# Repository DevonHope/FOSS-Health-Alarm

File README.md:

# NudgeBand

**A small, open-source wristband that wakes you up gently.**

Set a wake-up time, and NudgeBand watches how you move in your sleep. During the 30 minutes before
your alarm, it waits for a moment of light sleep and wakes you with a soft vibration on your wrist,
with no sound and no phone needed. If you never reach light sleep, it still wakes you at your set time.

Everything is open: the circuit boards, the 3D-printed case, the charging dock and the strap pattern.
You can build one yourself.

> **Status:** prototype PCBs ordered (November 2026). Nothing has been built or tested yet.
> See [Current status](#current-status).

---

## How it works

1. **You wear it to bed.** A low-power motion sensor (accelerometer) measures how much you move.
2. **It estimates your sleep stage.** Less movement usually means deeper sleep, and small movements
   usually mean light sleep.
3. **It picks the best moment.** In the 30-minute window before your alarm, it waits for light sleep,
   because waking from light sleep feels easier than waking from deep sleep.
4. **It nudges you awake.** A tiny vibration motor ramps up gently instead of buzzing suddenly.
5. **You put it on the dock.** The dock charges the band and is also used to load new firmware.

The band has no screen and no USB port. It is sealed except for four small gold contacts on the
underside that touch spring pins in the dock.

## What's in it

| Part | What it does |
| --- | --- |
| Nordic nRF54L10 | The main chip, with Bluetooth Low Energy built in |
| Motion sensor (accelerometer) | Tracks movement through the night |
| DRV2605L + 8 mm vibration motor | Gentle, ramped vibration |
| TI BQ25125 | Charges the battery |
| 60 mAh LiPo battery | Expected to last about a month per charge (estimate, not yet measured) |
| RGB LED | Shows status through a thin window in the case, with no hole |

- **Board:** 33 x 15 mm, 4-layer, assembled by JLCPCB
- **Case:** about 45 x 19 x 10 mm, 3D-printed in PETG, held shut by one M2 screw
- **Dock:** USB-C, magnets to hold the band in place, and a built-in programmer (RP2040 running `debugprobe`)
- **Strap:** 16 mm wide, sewn from a free pattern (Velcro or elastic with a buckle)

## Current status

*Last updated: 10 November 2026*

| Area | Status |
| --- | --- |
| Hardware design | ✅ Done. Band and dock **rev C** finished and reviewed (DRC/ERC clean) |
| PCBs | 📦 **Ordered.** Waiting for delivery |
| Case and dock housing | ✅ Designed. Ready to print and test-fit |
| Strap | ✅ Sewing patterns ready |
| Firmware | 🛠️ **Started.** Plan in [`firmware/TODO.md`](firmware/TODO.md); smart-wake logic written and unit-tested, drivers drafted, not yet run on hardware |
| Android app | 🧪 **First version** in [`android/`](android/). Works with a simulated band; Bluetooth spec in [`docs/ble-protocol.md`](docs/ble-protocol.md) |
| Testing | ⏳ Waits for boards. First checks: power-up, charging, radio range, vibration |

**Up next:** assemble the first boards when they arrive, print the case, bring up the firmware
(charger setup, motion sensor, vibration), then test smart-wake on real nights.

**Known limitations:**
- The radio and antenna are not certified (FCC, IC or CE). Treat it as a personal project, not a product.
- The antenna may need tuning on the first boards.
- Battery life is a datasheet estimate until it is measured.

## Repository layout

```
hardware/
├── band/      the wristband: PCB, case and contact carrier for each revision (build rev C)
├── dock/      the charging and programming dock: PCB and housing for each revision (build rev C)
├── strap/     strap sewing patterns (PDF)
├── reviews/   design reviews of the boards
└── tools/     helper scripts (e.g. printability check)
android/       the Android companion app (and a simulated band for testing)
firmware/      band firmware (Zephyr): plan in TODO.md, source, unit tests
docs/          roadmap, parts research, design notes and the Bluetooth protocol
```

Older revisions (A and B) are kept for reference. Each folder has its own README with details.
[`hardware/README.md`](hardware/README.md) lists exactly what to order and what to print.

## Building one

1. **Order the boards.** Use the fab files in `hardware/band/rev-c/pcb/fab/` and `hardware/dock/rev-c/pcb/fab/`
   (JLCPCB with assembly), plus the small contact-carrier board.
2. **Buy the extras.** Spring pins, magnets, battery and motor are listed in
   [`BUY-LIST.md`](hardware/band/rev-a/contact-carrier/BUY-LIST.md).
3. **Print the case and dock** in PETG. Print notes are in each `case/` folder.
4. **Sew the strap** from the pattern in `hardware/strap/`.
5. **Flash the firmware** through the dock (see [`firmware/README.md`](firmware/README.md); not ready yet).

Design tools: KiCad 10 for the PCBs, Python scripts for the case models.

## License

[MIT](LICENSE). Use it, change it and share it.

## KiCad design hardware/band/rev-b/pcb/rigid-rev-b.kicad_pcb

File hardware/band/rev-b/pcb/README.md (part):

> **Superseded by rev C** (2026-11-08 review fixes): [`../../rev-c/pcb`](../../rev-c/pcb)

# WakeBand rigid rev B (KiCad 10 project)

Rev B is rev A rebuilt so that **JLCPCB assembles every part** (no consigned module). It keeps rev
A's 33 x 15 mm outline, 4-layer 0.8 mm stackup (JLC04081H-7628), case, dock, contact carrier and
strap: the four B-side dock landings (J601 1-4 at x 131.5), the LED position (D702) and the cell and
LRA lead pads (TP201/TP202, TP501/TP502, JP201) are where rev A had them.

**Not FCC/IC (or CE) certified.** The radio is a bare nRF54L10 with a chip antenna on our own board,
so the module certification rev A could lean on does not apply. Build it for personal use and
experiments only; don't sell or distribute it as a product.

**Status (2026-11-08):** schematic, placement and routing done. ERC 0; DRC 0 at every severity
(errors and warnings), 0 unconnected, schematic parity 0. Trace audit clean except one forced
0.2 mm jog (see Routing). Not built or tested yet.

## What changed from rev A

| Rev A | Rev B | Why |
| --- | --- | --- |
| ISP2454 module (radio + antenna) | **nRF54L10-QFAA** (C44800139) + Nordic's QFN48 reference circuit + Johanson **2450AT18A0100001E** chip antenna (C17430588) | Module not stocked at JLC. The nRF54L15 (C42458750) is out of stock at JLC and LCSC (0 on 2026-11-07); the L10 has the same package, pins and reference circuit, with 1 MB RRAM / 192 KB RAM. An nRF54L05 or nRF54L15 drops in unchanged. |
| nPM1304 PMIC | **BQ25125** (C2871567) | Same family and pinout as the BQ25120A (C2866577, only 4 at JLC). 4.2 V charge, 30 mA set by R202, 1.8 V buck on at power-up (unused here), LS/LDO switches the LED's supply. **No fuel gauge** (the nPM1304 had one): firmware estimates charge from the BQ's VBMON battery-voltage reading. |
| KTD2026 LED driver | **IS31FL3193** (C2653363) | Stocked; its I2C inputs work on the 2.0 V bus (VIH 1.4 V). |
| 2.0 V rail (nPM1304 buck) | **2.0 V from a TPS7A0220 LDO** (U203, C2860934) on PMID | The BQ25125 buck is 1.8 V +/- 2.5 % (1.755 V worst case), too close to the nRF54L10's 1.75 V power-on-reset minimum, and a board that fails reset can't run firmware to fix it. The LDO is 2.0 V +/- 1.5 % (1.97 V minimum), draws 25 nA, and sits in a 1 x 1 mm X2SON. The buck stays fitted but unloaded (VSYS). A BQ2512x with a higher default (BQ25121A, 2.5 V) has 1 in stock. |
| DRV2605L on VSYS | DRV2605L on **VBAT** | Straight from the cell (2.0-5.2 V). |
| UART pads beside the dock landings, debug LED D701 | **removed** (J601 has the 4 dock landings only) | No routing room at the dock end. Logs go over **SEGGER RTT through the SWD dock pins** (see Firmware setup). |
| I2C/2.0 V test pads TP702-TP704 | removed | Probe R203/R204 and any 2.0 V capacitor instead. |
| R209, R210 (/INT and /PG pull-ups) | removed | No routing room; use the nRF54L10's internal pull-ups on P1.05 and P1.06. |
| KTD2026 on VSYS | IS31FL3193 VCC on **PMID** | Always powered on battery, so its I2C inputs (rated to VCC + 0.3 V) never clamp the shared bus. |

Unchanged: LIS2DW12, DRV2605L, ESD (TPD1E10B06 x4, SMF12A), the dock series resistors.

## nRF54L10 pin map

| Pin | Port | Net | Notes |
| --- | --- | --- | --- |
| 5 | P1.04 | I2C_SCL | clock-capable pin (TWIM needs both lines on clock pins) |
| 9 | P1.08 | I2C_SDA | clock-capable |
| 6 | P1.05 | PMIC_INT | BQ25125 /INT, wake from System OFF (P1) |
| 7 | P1.06 | DOCK_PG | BQ25125 /PG: low while the dock supplies VIN |
| 8 | P1.07 | HAPT_EN | DRV2605L EN |
| 27 | P0.02 | ACC_INT1 | LIS2DW12 INT1, wake (P0) |
| 24 | P0.01 | ACC_INT2 | LIS2DW12 INT2, wake; also TP401 |
| 38 | P1.10 | LED_EN | IS31FL3193 SDB (R211 pulls it low) |
| 39 | P1.11 | CHG_CD | BQ25125 /CD |
| 13 | P2.02 | LS_CTRL | BQ25125 LSCTRL (LED driver supply) |
| 25 / 26 / 30 | SWDIO / SWDCLK / nRESET | dock pins 3/4; TP701 |
| 1 / 2 | XL1 / XL2 | 32.768 kHz crystal X1 |
| 34 / 35 | XC1 / XC2 | 32 MHz crystal X2 |

The pins were chosen for the layout: each signal leaves the QFN on the side facing where it goes.
P1.02/P1.03 (NFC), P2.07/P2.08 and P1.09 (rev A's UART and debug LED) and the other GPIOs are unconnected.

I2C addresses: LIS2DW12 0x19, DRV2605L 0x5A, IS31FL3193 0x68, BQ25125 0x6A.

## Firmware setup

### Logs: SEGGER RTT, no UART

Rev B has no UART pads. Log over **RTT** through the SWD dock pins (J601 3/4) with any J-Link or
the nRF54L DK's on-board debugger: in Zephyr set `CONFIG_USE_SEGGER_RTT=y`, `CONFIG_LOG_BACKEND_RTT=y`
and `CONFIG_UART_CONSOLE=n` (or `CONFIG_RTT_CONSOLE=y`), then read with `JLinkRTTViewer` or
`west rtt`. RTT works on the dock while the band charges. Disable it in release builds so the
debug domain powers down.

### nRF54L10

- **DC/DC:** the board has Nordic's DC/DC inductor (L1 4.7 uH), and all of Nordic's current figures
  assume DC/DC. Turn it on early (`REGULATORS.VREGMAIN.DCDCEN = 1`; in Zephyr set
  `regulator-initial-mode = <NRF5X_REG_MODE_DCDC>` on `&vregmain`).
- **Clocks:** both crystals use the chip's internal load capacitors (no external caps).
  - X1, 32.768 kHz: CL 9 pF.
  - X2, 32 MHz: CL 8 pF.
  - Set `&lfxo` / `&hfxo` to `load-capacitance = "internal"` with the value for each crystal's CL (datasheet INTCAP formula).
  - Use the LFXO as the LF clock source: only the LFXO keeps the GRTC running in System OFF.
- **RF:** the matching network is the board's own (see "Antenna tuning"); leave TX power at 0 dBm
  until it is tuned.
- **NFC pins:** unused; leave NFC disabled.
- **PMIC_INT (P1.05):** enable the internal pull-up (no external resistor). /INT is open drain; with
  EN_INT cleared it only pulses low for 128 us on events.
- **DOCK_PG (P1.06):** enable the internal pull-up (about 13 kOhm; there's no external
  resistor). /PG is open drain and low only while docked, so the pull-up draws about 140 uA
  from the dock and nothing on battery.

### BQ25125

- **/CD:** the BQ25125 talks I2C on battery only while /CD is high.
  - Drive CHG_CD high to configure it. Drive it low to idle: that is Hi-Z mode, where the BQ draws 0.7-0.75 uA. The 2.0 V rail comes from U203 on PMID, so it is unaffected.
  - The buck's 1.8 V output (VSYS) powers nothing, but **leave it on**: the BQ's /CD and LSCTRL input
    thresholds are 0.25 / 0.75 x VSYS, so with SYS off the nRF couldn't reliably drive them. (The I2C
    threshold is 0.75 x the pull-up voltage, 1.5 V on the 2.0 V bus; /CD at 2.0 V is above 0.75 x 1.8 V.)
  - Also drive it low while docked (DOCK_PG low), because /CD high stops charging.
- **Defaults:** without I2C the charger already does the right thing.
  - 1.8 V buck on (unused).
  - 4.2 V charge.
  - 30 mA from R202 (6.65 k) in default mode.
  - 2 mA termination (IPRETERM to GND).
  - 100 mA input limit (ILIM to GND).
  - NTC (TS) enabled.
- **After the first I2C write it is in host mode**, and its 50 s watchdog applies. Write, then re-write at least every 50 s while /CD is high:
  - Charge current 30 mA (reg 0x03, as for the BQ25120A).
  - Termination.
  - EN_INT = 0 in reg 0x02, so /INT pulses instead of staying low through the whole charge.
- **LED supply:** the LED anode (VLED) is on the BQ25125's LS/LDO output, which powers up as a
  1.8 V LDO, too low to light the LED. Write reg 0x07 for load-switch mode (VLED then follows PMID),
  then raise LS_CTRL. The watchdog undoes this after 50 s without I2C in host mode: the LED just
  goes dark, nothing is damaged.
- **Battery level:** read VBMON (reg 0x0A): the battery voltage as a percentage of VBATREG, in 2 % steps.
- **Ship mode:** with VIN absent, /CD high and /MR high, write EN_SHIPMODE. The cell then sees about 2 nA (the DRV2605L on VBAT adds its shutdown current). The dock (VIN) or shorting TP203 (/MR) to GND wakes it; the nRF54L10 then starts from reset.

### IS31FL3193

- **Shutdown by default:** it starts in software shutdown (reg 0x00). Write EN = 1, SSD = 0, set the current with reg 0x03 (e.g. 5 mA), then write PWM and the update register 0x07.
- **Channels:** OUT1 is green, OUT2 blue, OUT3 red (assigned for routing).
- **Supply:** VCC is on PMID (always up on battery), so the I2C bus is never clamped by an
  unpowered driver. Drive LED_EN (SDB) high to wake it. The LED anode is on VLED, which needs
  LS_CTRL on in load-switch mode (see above).

## Antenna tuning

The radio output runs: ANT pin -> Nordic's low-pass ladder (L2 2.7 nH, C6 1.5 pF, L3 3.5 nH, C9 2.0 pF,
L4 3.5 nH, C11 0.3 pF; their exact 0201 parts and placement) -> RF_50 -> **tuning network** -> antenna:

| Part | Position | Fitted | Role |
| --- | --- | --- | --- |
| C14 (0402) | RF_50 to GND, at the ladder end | not fitted | pi shunt 1 |
| R2 (0402) | series, RF_50 to ANT_FEED | 0 ohm | pi series (a 0402 inductor or capacitor) |
| C15 (0402) | ANT_FEED to GND, at the antenna side | not fitted | pi shunt 2 |

The antenna (AE1) sits in a 4.2 x 5.9 mm corner (x 100-104.2, y 109.1-115) with no copper on any
layer (rule area "Antenna keep-out"); the 50-ohm feed (0.36 mm on F.Cu over the In1 ground, 0.16 mm
gap) enters it from the ground edge. Johanson's evaluation board uses 6.5 x 6.5 mm and its own
match, so this board needs its own values. Expect less range than the datasheet until it is tuned.

**Tune with the cell, case, strap and wrist (or a hand) in place:** the plastic, the cell and the
body all pull the antenna down in frequency.

With a VNA (best):
1. Cut the feed at R2: lift R2 and solder a 0402-pad pigtail (a short 1.13 mm coax, shield to the
   C15/C14 ground pads, centre to the AE1 side of R2). Calibrate at the coax end (port extension).
2. Measure S11 of the antenna from 2.3 to 2.6 GHz with the band assembled and on the wrist.
3. Use a Smith-chart tool (e.g. SimSmith or Johanson's own) to pick an L-match with C15 and R2 (or
   a pi with C14) that moves 2.44 GHz to 50 ohm; Murata LQP03/LQG15 inductors and GJM capacitors
   come in 0.1 nH / 0.1 pF steps. Typical starting points for this antenna: series 2-4 nH, shunt
   0.5-1.5 pF.
4. Fit the parts, put R2 back as the series part and re-measure. Aim for S11 below -10 dB across
   2.402-2.480 GHz.

Without a VNA (RSSI method):
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
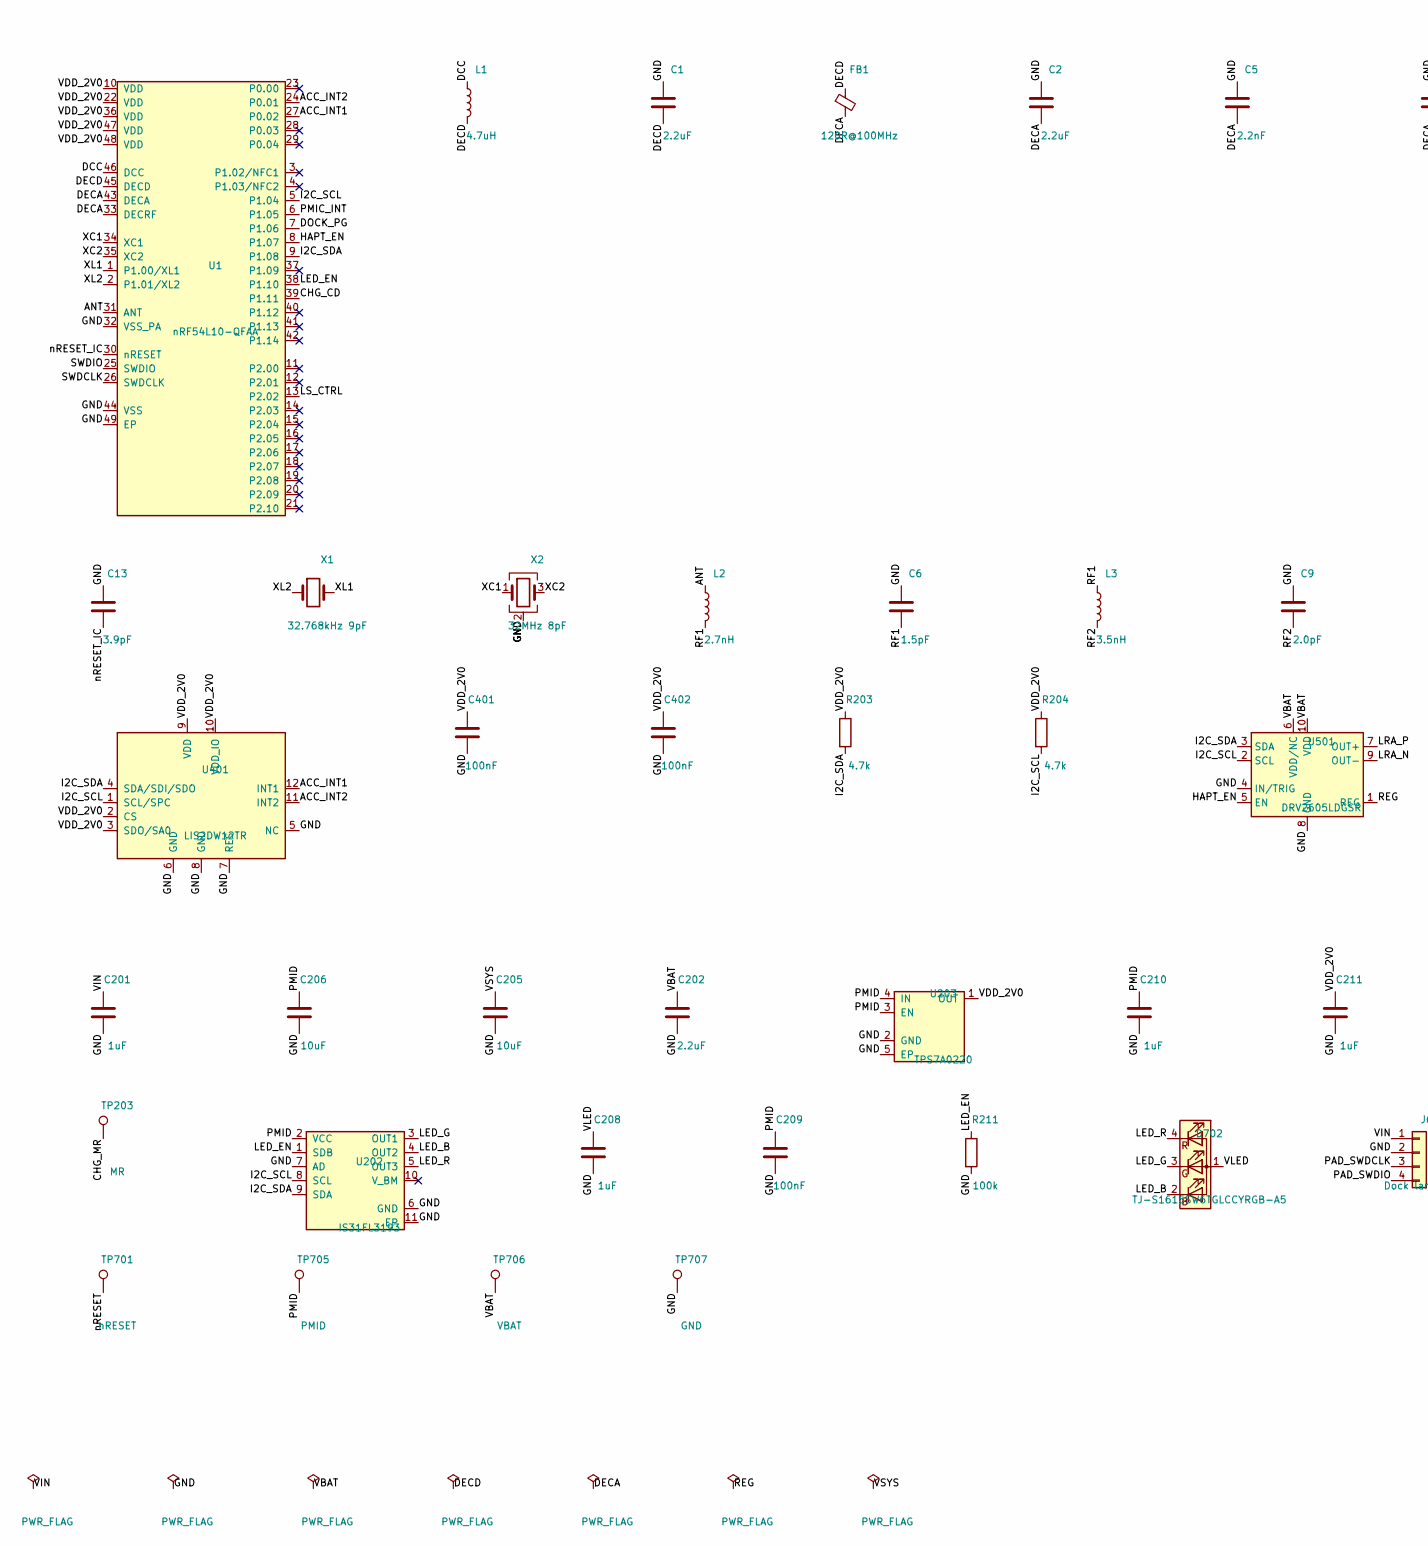
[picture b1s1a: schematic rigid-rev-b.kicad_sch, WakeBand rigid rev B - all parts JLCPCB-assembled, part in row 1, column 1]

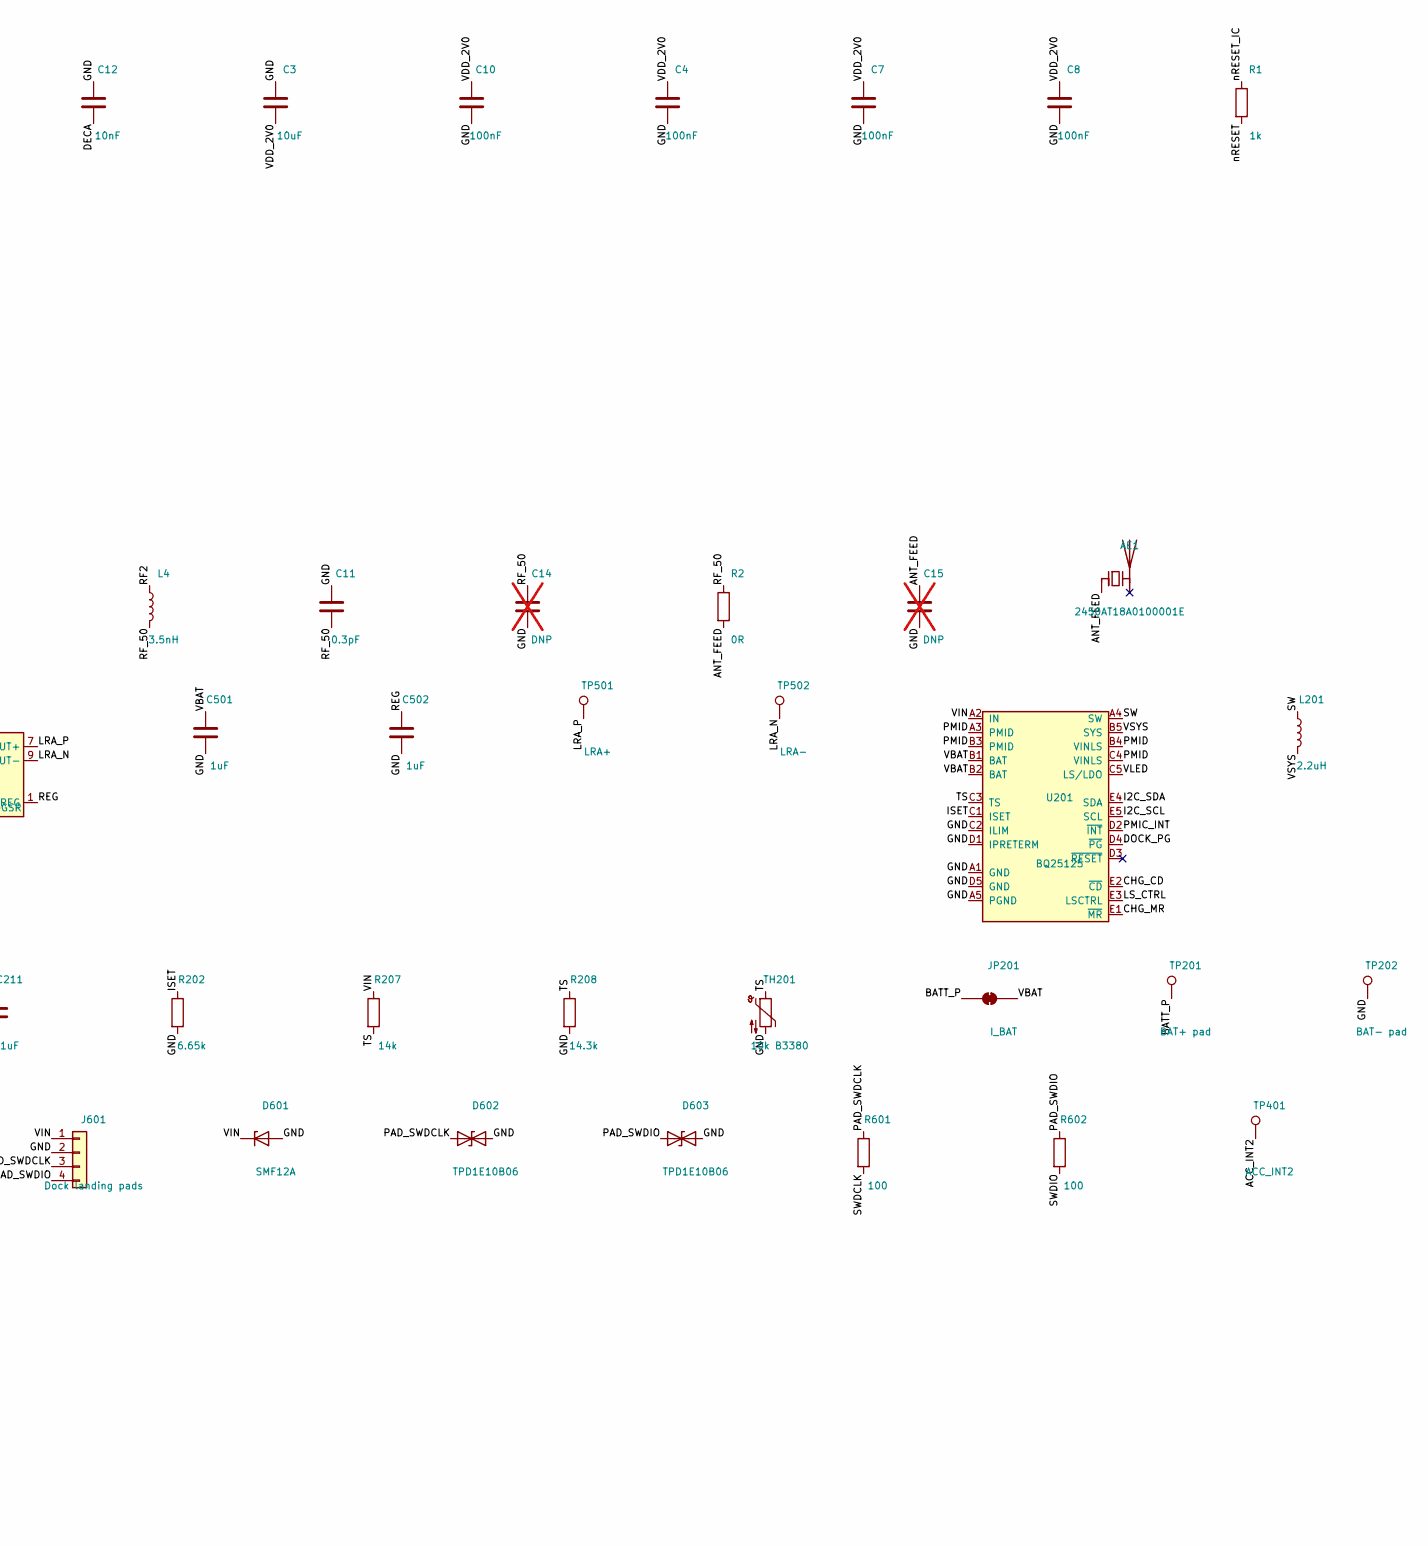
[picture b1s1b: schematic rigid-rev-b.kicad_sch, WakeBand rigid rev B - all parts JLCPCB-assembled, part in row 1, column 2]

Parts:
AE1: 2450AT18A0100001E; Johanson_2450AT18x100; MPN Johanson 2450AT18A0100001E; LCSC C17430588
C1, C2: 2.2uF; Nordic_CAPC0603X03L_C; MPN Murata GRM033R61A225KE47D; LCSC C335106
C3: 10uF; Nordic_CAPC1005X04L; LCSC C15525
C4, C7, C8, C10: 100nF; Nordic_CAPC0603X03L_C; LCSC C307380
C5: 2.2nF; Nordic_CAPC0603X03L_C; MPN Murata GRM033R71A222KA01D; LCSC C161479
C6: 1.5pF; Nordic_CAPC0603X03L_C; MPN Murata GJM0335C1E1R5WB01D; LCSC C435397
C9: 2.0pF; Nordic_CAPC0603X03L_C; MPN Murata GJM0335C1E2R0WB01D; LCSC C668326
C11: 0.3pF; Nordic_CAPC0603X03L_C; MPN Murata GRM0335C1HR30BA01D; LCSC C76927
C12: 10nF; Nordic_CAPC0603X03L_C; MPN Murata GRM033R71A103KA01D; LCSC C76941
C13: 3.9pF; Nordic_CAPC0603X03L_C; MPN Murata GRM0335C1H3R9CA01D; LCSC C76926
C14, C15: DNP; C_0402_1005Metric; not fitted
C201, C208, C501, C502: 1uF; C_0402_1005Metric; LCSC C52923
C202: 2.2uF; C_0603_1608Metric; LCSC C23630
C205, C206: 10uF; C_0603_1608Metric; LCSC C96446
C209, C401, C402: 100nF; C_0402_1005Metric; LCSC C1525
C210, C211: 1uF; Nordic_CAPC0603X03L_C; MPN Samsung CL03A105MO3NRNH; LCSC C307385
D601: SMF12A; D_SOD-123F; MPN Littelfuse SMF12A; LCSC C207255
D602, D603: TPD1E10B06; Texas_DPY0002A_0.6x1mm_P0.65mm; MPN TI TPD1E10B06DPYR; LCSC C48260
D702: TJ-S1615SW6TGLCCYRGB-A5; LED_TOGIALED_1615_RGB_CommonAnode; MPN TOGIALED TJ-S1615SW6TGLCCYRGB-A5; LCSC C273610
FB1: 120R@100MHz; Nordic_INDC0603X03L_C; MPN Murata BLM03AG121SN1D; LCSC C97850
J601: Dock landing pads; DockLanding_4xB_D1.6mm
JP201: I_BAT; SolderJumper-2_P1.3mm_Bridged_RoundedPad1.0x1.5mm
L1: 4.7uH; Nordic_INDC1608X06L; MPN TDK MLZ1608M4R7WT000; LCSC C76799
L2: 2.7nH; Nordic_INDC0603X03L_C; MPN Murata LQP03HQ2N7B02D; LCSC C7216765
L3, L4: 3.5nH; Nordic_INDC0603X03L_C; MPN Murata LQP03HQ3N5B02D; LCSC C3911055
L201: 2.2uH; L_Murata_DFE201610P; MPN Murata DFE201610E-2R2M; LCSC C337891
R1: 1k; Nordic_RESC0603X03L_C; LCSC C270365
R2: 0R; R_0402_1005Metric; LCSC C17168
R202: 6.65k; R_0402_1005Metric; LCSC C45194
R203, R204: 4.7k; R_0402_1005Metric; LCSC C25900
R207: 14k; R_0402_1005Metric; LCSC C54831
R208: 14.3k; R_0402_1005Metric; LCSC C25855
R211: 100k; R_0402_1005Metric; LCSC C25741
R601, R602: 100; R_0402_1005Metric; LCSC C25076
TH201: 10k B3380; R_0402_1005Metric; MPN Murata NCP15XH103F03RC; LCSC C77131
TP201: BAT+ pad; TestPoint_Pad_2.0x2.0mm
TP202: BAT- pad; TestPoint_Pad_1.5x1.5mm
TP203: MR; TestPoint_Pad_D0.8mm
TP401: ACC_INT2; TestPoint_Pad_D0.8mm
TP501: LRA+; Pad_SMD_1.0x1.5mm
TP502: LRA-; Pad_SMD_1.0x1.5mm
TP701: nRESET; TestPoint_Pad_D0.8mm
TP705: PMID; TestPoint_Pad_D0.8mm
TP706: VBAT; TestPoint_Pad_D0.8mm
TP707: GND; TestPoint_Pad_D0.8mm
U1: nRF54L10-QFAA; Nordic_QFN40P600X600X90-48N; MPN Nordic NRF54L10-QFAA-R7; LCSC C44800139
U201: BQ25125; TI_DSBGA-25_2.5x2.5mm_Layout5x5_P0.4mm; MPN TI BQ25125YFPR; LCSC C2871567
U202: IS31FL3193; DFN-10-1EP_3x3mm_P0.5mm_EP1.65x2.38mm; MPN Lumissil IS31FL3193-DLS2-TR; LCSC C2653363
U203: TPS7A0220; Texas_X2SON-4_1x1mm_P0.65mm_SilkTrim; MPN TI TPS7A0220PDQNR; LCSC C2860934
U401: LIS2DW12TR; LGA-12_2x2mm_P0.5mm; MPN ST LIS2DW12TR; LCSC C189624
U501: DRV2605LDGSR; TSSOP-10_3x3mm_P0.5mm; MPN TI DRV2605LDGSR; LCSC C527464
X1: 32.768kHz 9pF; Nordic_XTAL_2012; MPN Epson FC-12M X1A0000610008; LCSC C96341
X2: 32MHz 8pF; Nordic_BT-XTAL_2016; MPN Yangxing XL7EL89CKI-111YLC-32M; LCSC C2965582

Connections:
/ACC_INT1: U1.27 (P0.02), U401.12 (INT1)
/ACC_INT2: TP401.1, U1.24 (P0.01), U401.11 (INT2)
/ANT: L2.1, U1.31 (ANT)
/ANT_FEED: AE1.1 (FEED), C15.1, R2.2
/BATT_P: JP201.1 (A), TP201.1
/CHG_CD: U1.39 (P1.11), U201.E2 (~CD)
/CHG_MR: TP203.1, U201.E1 (~MR)
/DCC: L1.1, U1.46 (DCC)
/DECA: C2.2, C5.2, C12.2, FB1.2, U1.33 (DECRF), U1.43 (DECA)
/DECD: C1.2, FB1.1, L1.2, U1.45 (DECD)
/DOCK_PG: U1.7 (P1.06), U201.D4 (~PG)
/GND: C1.1, C2.1, C3.1, C4.2, C5.1, C6.1, C7.2, C8.2, C9.1, C10.2, C11.1, C12.1, C13.1, C14.2, C15.2, C201.2, C202.2, C205.2, C206.2, C208.2, C209.2, C210.2, C211.2, C401.2, C402.2, C501.2, C502.2, D601.2 (A), D602.2 (A2), D603.2 (A2), J601.2, R202.2, R208.2, R211.2, TH201.2, TP202.1, TP707.1, U1.32 (VSS_PA), U1.44 (VSS), U1.49 (EP), U201.A1 (GND), U201.A5 (PGND), U201.C2 (ILIM), U201.D1 (IPRETERM), U201.D5 (GND), U202.6 (GND), U202.7 (AD), U202.11 (EP), U203.2 (GND), U203.5 (EP), U401.5 (NC), U401.6 (GND), U401.7 (RES), U401.8 (GND), U501.4 (IN/TRIG), U501.8 (GND), X2.2 (G), X2.4 (G)
/HAPT_EN: U1.8 (P1.07), U501.5 (EN)
/I2C_SCL: R204.2, U1.5 (P1.04), U201.E5 (SCL), U202.8 (SCL), U401.1 (SCL/SPC), U501.2 (SCL)
/I2C_SDA: R203.2, U1.9 (P1.08), U201.E4 (SDA), U202.9 (SDA), U401.4 (SDA/SDI/SDO), U501.3 (SDA)
/ISET: R202.1, U201.C1 (ISET)
/LED_B: D702.2 (BK), U202.4 (OUT2)
/LED_EN: R211.1, U1.38 (P1.10), U202.1 (SDB)
/LED_G: D702.3 (GK), U202.3 (OUT1)
/LED_R: D702.4 (RK), U202.5 (OUT3)
/LRA_N: TP502.1, U501.9 (OUT-)
/LRA_P: TP501.1, U501.7 (OUT+)
/LS_CTRL: U1.13 (P2.02), U201.E3 (LSCTRL)
/PAD_SWDCLK: D602.1 (A1), J601.3, R601.1
/PAD_SWDIO: D603.1 (A1), J601.4, R602.1
/PMIC_INT: U1.6 (P1.05), U201.D2 (~INT)
/PMID: C206.1, C209.1, C210.1, TP705.1, U201.A3 (PMID), U201.B3 (PMID), U201.B4 (VINLS), U201.C4 (VINLS), U202.2 (VCC), U203.3 (EN), U203.4 (IN)
/REG: C502.1, U501.1 (REG)
/RF1: C6.2, L2.2, L3.1
/RF2: C9.2, L3.2, L4.1
/RF_50: C11.2, C14.1, L4.2, R2.1
/SW: L201.1, U201.A4 (SW)
/SWDCLK: R601.2, U1.26 (SWDCLK)
/SWDIO: R602.2, U1.25 (SWDIO)
/TS: R207.2, R208.1, TH201.1, U201.C3 (TS)
/VBAT: C202.1, C501.1, JP201.2 (B), TP706.1, U201.B1 (BAT), U201.B2 (BAT), U501.6 (VDD/NC), U501.10 (VDD)
/VDD_2V0: C3.2, C4.1, C7.1, C8.1, C10.1, C211.1, C401.1, C402.1, R203.1, R204.1, U1.10 (VDD), U1.22 (VDD), U1.36 (VDD), U1.47 (VDD), U1.48 (VDD), U203.1 (OUT), U401.2 (CS), U401.3 (SDO/SA0), U401.9 (VDD), U401.10 (VDD_IO)
/VIN: C201.1, D601.1 (K), J601.1, R207.1, U201.A2 (IN)
/VLED: C208.1, D702.1 (A), U201.C5 (LS/LDO)
/VSYS: C205.1, L201.2, U201.B5 (SYS)
/XC1: U1.34 (XC1), X2.1
/XC2: U1.35 (XC2), X2.3
/XL1: U1.1 (P1.00/XL1), X1.2
/XL2: U1.2 (P1.01/XL2), X1.1
/nRESET: R1.2, TP701.1
/nRESET_IC: C13.2, R1.1, U1.30 (nRESET)

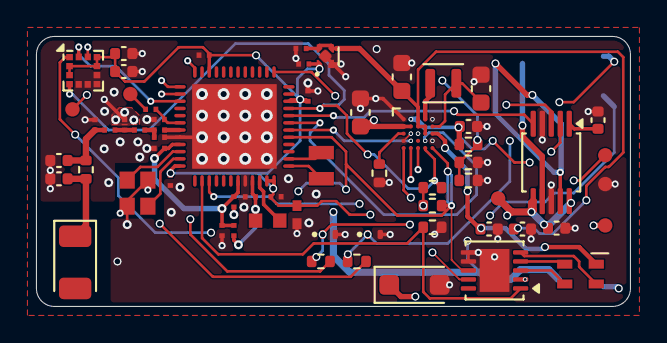
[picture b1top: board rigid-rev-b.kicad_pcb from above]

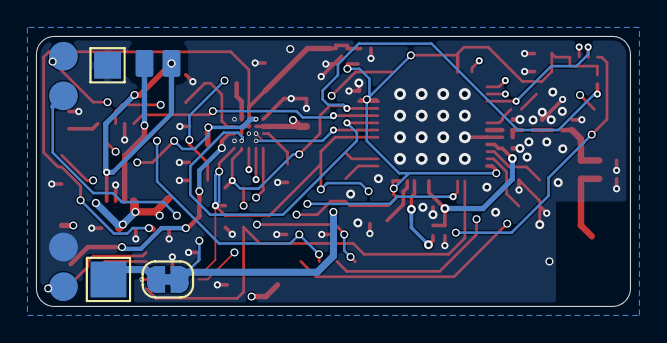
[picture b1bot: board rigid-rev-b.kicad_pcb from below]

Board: 4 copper layers, 33.0 x 15.0 mm, 69 parts (5 on the bottom side), 46 nets.

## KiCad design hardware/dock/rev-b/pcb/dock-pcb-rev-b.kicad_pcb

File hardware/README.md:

# WakeBand hardware

Everything is grouped by **what it is** (band or dock), then **revision**, then **PCB or printed case**:
every revision folder carries its own `pcb/` and its own `case/` (the models to print).
Build **rev C** (rev B plus the 2026-11-08 review fixes; every part assembled by JLCPCB). Rev A and rev B are
kept unchanged for reference: a new revision always gets its own folder.

```
hardware/
├── band/                    the wristband
│   ├── rev-a/
│   │   ├── pcb/             rigid band board, ISP2454 module (rigid-rev-a.kicad_pro)
│   │   ├── case/            shell + wrist cover (print)
│   │   └── contact-carrier/ small PCB holding the 4 spring pins in the cover, + BUY-LIST.md
│   ├── rev-b/               superseded by rev C (as reviewed on 2026-11-08)
│   │   ├── pcb/             rigid band board, nRF54L10 bare chip (rigid-rev-b.kicad_pro)
│   │   ├── case/            rev B shell + wrist cover
│   │   └── contact-carrier/ same carrier as rev A
│   ├── rev-c/               rev B + 2026-11-08 review fixes: build this
│   │   ├── pcb/             rigid band board (rigid-rev-c.kicad_pro)
│   │   ├── case/            shell + wrist cover, same geometry as rev B (print)
│   │   └── contact-carrier/ same carrier as rev A and rev B
│   └── archive/flex-rev-a/  early flex-PCB design (not built)
├── dock/                    the charging / programming dock
│   ├── rev-a/
│   │   ├── pcb/             dock PCB (dock-pcb-rev-a.kicad_pro)
│   │   └── case/            dock housing rev A (superseded)
│   ├── rev-b/               superseded by rev C (as reviewed on 2026-11-08)
│   │   ├── pcb/             dock PCB, rev A circuit, stocked pins (dock-pcb-rev-b.kicad_pro)
│   │   └── case/            dock housing rev B
│   └── rev-c/               rev B + 2026-11-08 review fixes: build this
│       ├── pcb/             dock PCB with pin ESD, decoupling, no vias under paste (dock-pcb-rev-c.kicad_pro)
│       └── case/            dock housing rev C (print)
├── reviews/                 design reviews (latest: 2026-11-08, two advisors per board)
├── strap/                   strap sewing patterns
└── tools/                   printcheck.py (printability check for the printed parts)
```

## What to order and print (rev C)

| What | Where | How |
| --- | --- | --- |
| Band PCB, assembled | [`band/rev-c/pcb/fab/jlcpcb/`](band/rev-c/pcb/fab/jlcpcb) | JLCPCB Standard PCBA, 2 panels of 2 x 2 (see its README, "Ordering") |
| Contact carrier PCB | [`band/rev-c/contact-carrier/fab/`](band/rev-c/contact-carrier/fab) | bare PCB, panel of 6, 1.6 mm |
| Dock PCB, assembled | [`dock/rev-c/pcb/fab/dock-pcb-rev-c-fab.zip`](dock/rev-c/pcb/fab) | JLCPCB, top side (BOM + CPL inside the zip) |
| Spring pins, magnets, feet, glue | [`band/rev-a/contact-carrier/BUY-LIST.md`](band/rev-a/contact-carrier/BUY-LIST.md) | Mouser, Indigo |
| Band shell | [`band/rev-c/case/wakeband-case-rev-c-shell.stl`](band/rev-c/case) | PETG, top face down, no supports |
| Wrist cover | [`band/rev-c/case/wakeband-case-rev-c-cover.stl`](band/rev-c/case) | PETG, wrist face down, pause at z 1.25 mm for the magnets |
| Dock top plate and tray | [`dock/rev-c/case/`](dock/rev-c/case) (`-top.stl`, `-tray.stl`) | PETG, flat faces down, no supports |
| Strap | [`strap/`](strap) | sewing pattern PDFs |

Each folder's README has the details: firmware notes and antenna tuning (band PCB), assembly (case),
flashing the dock and programming the band (dock PCB).

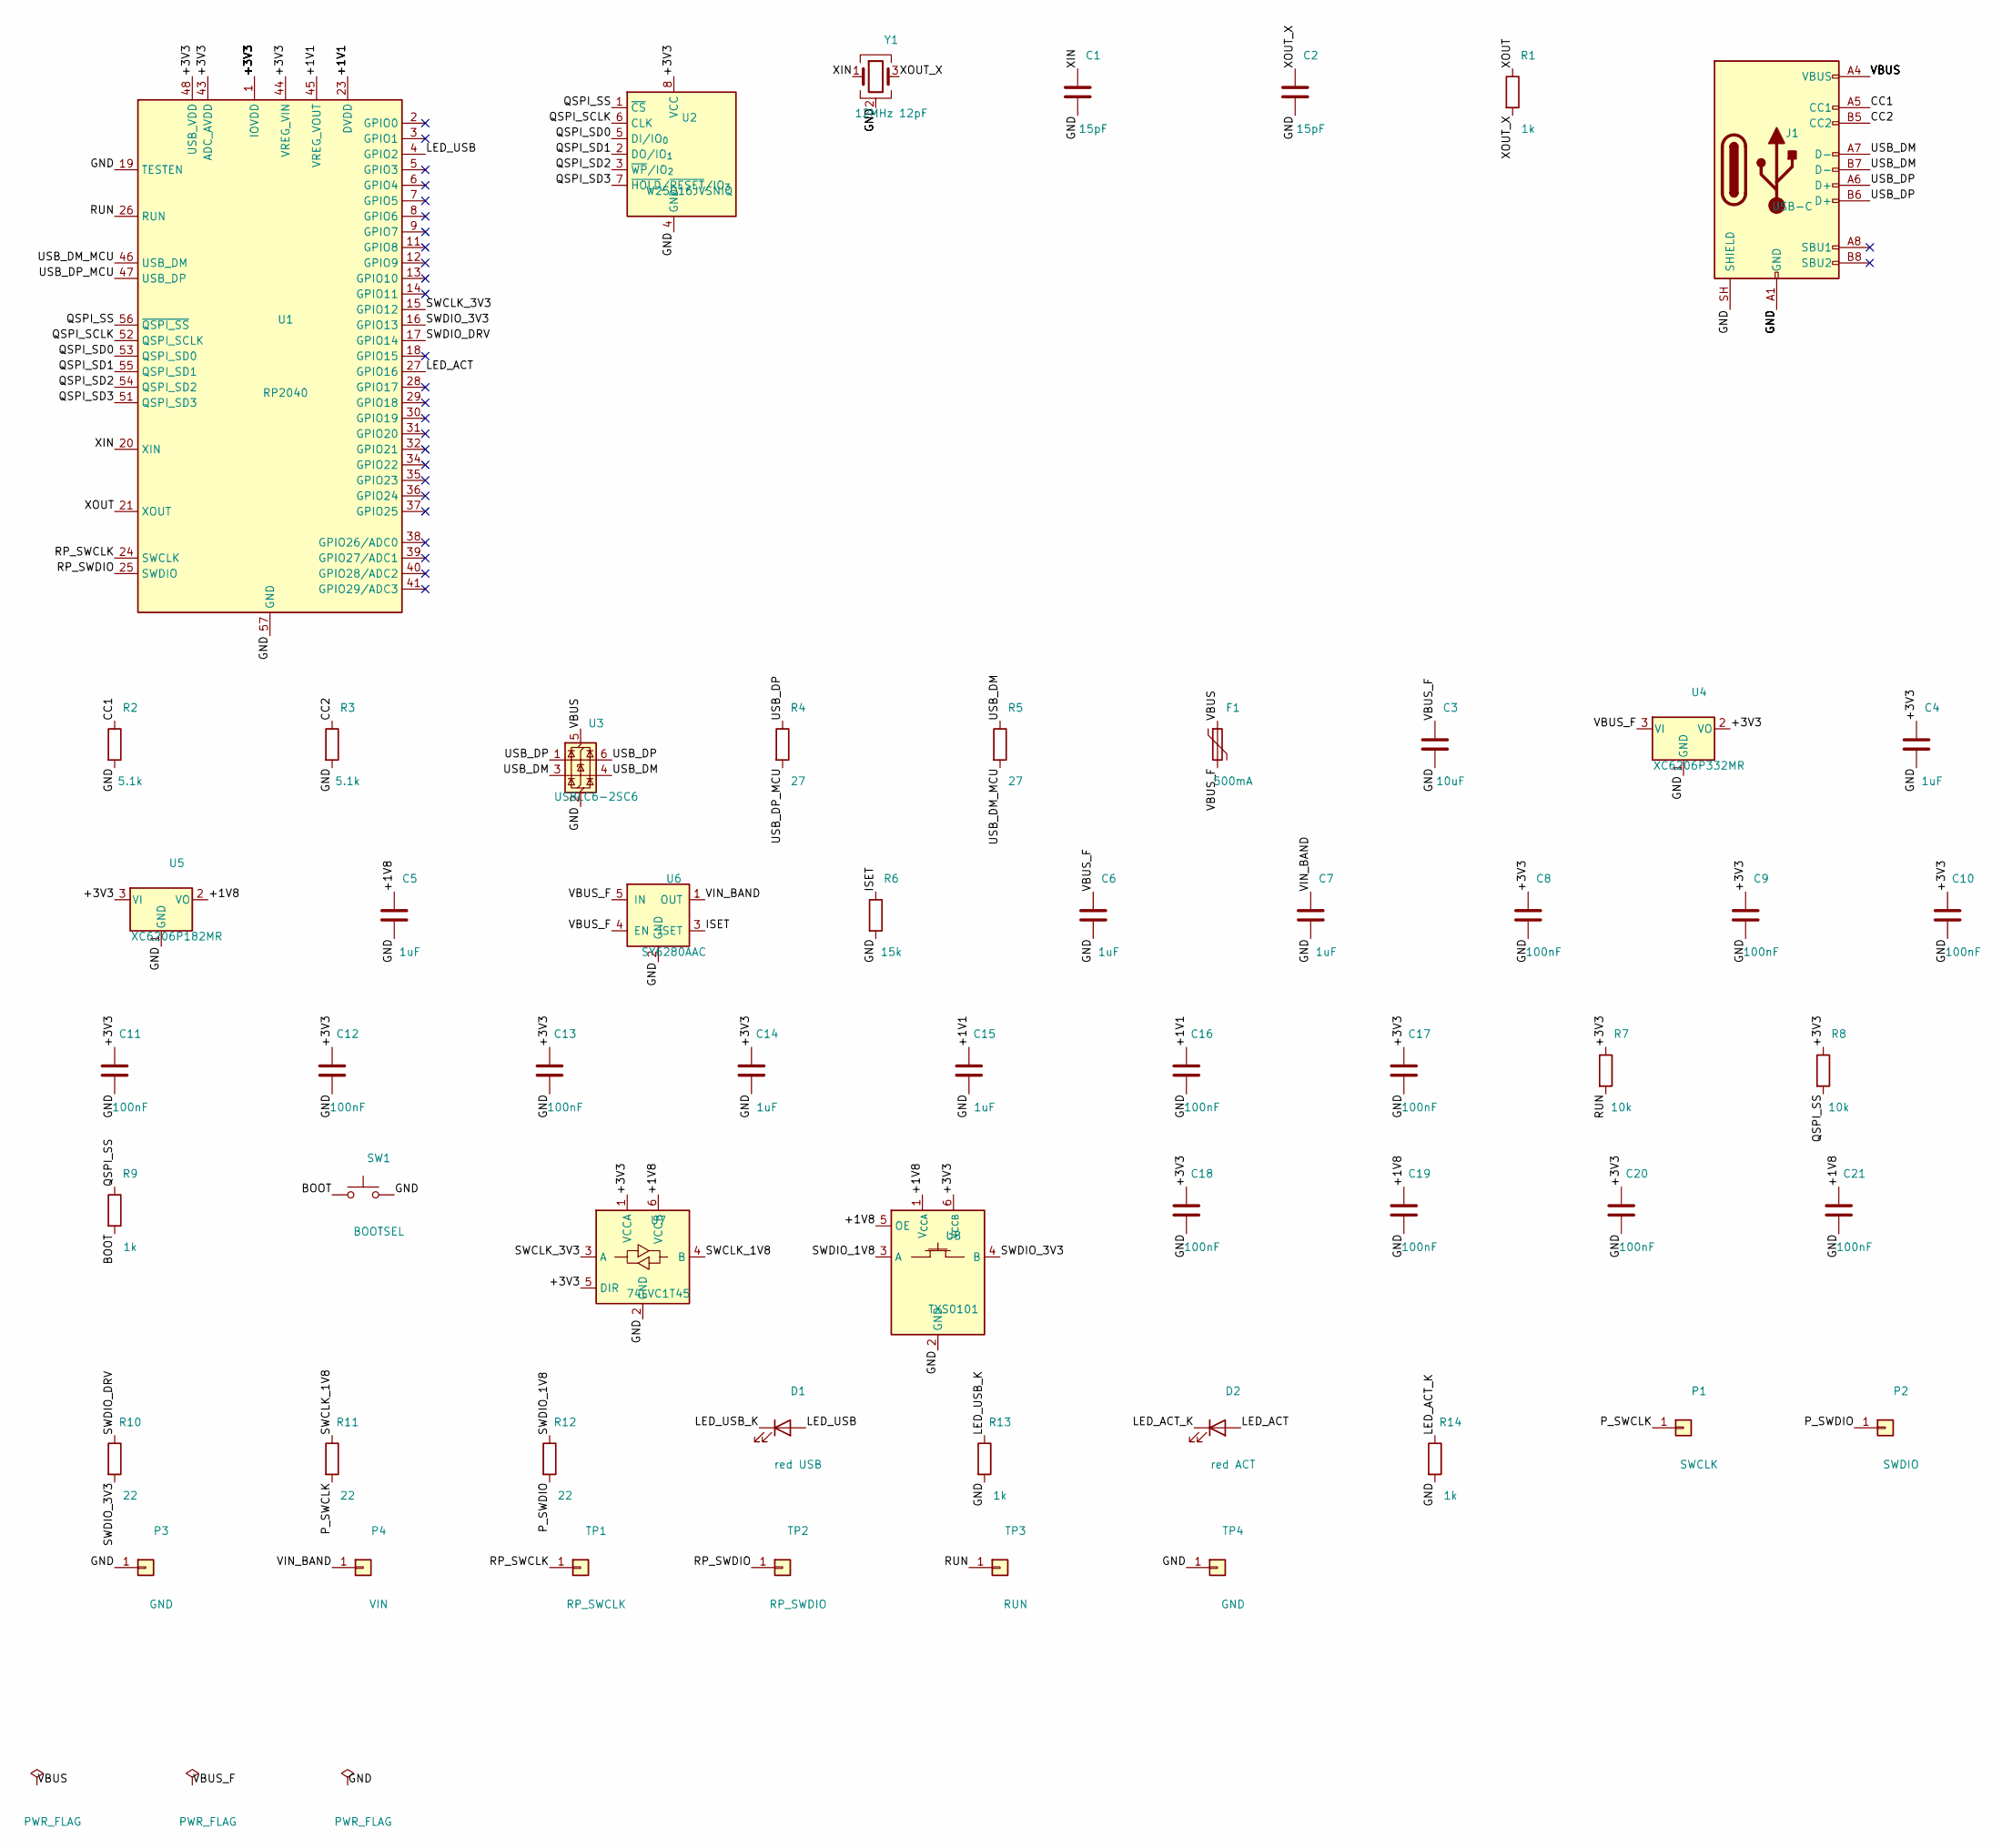
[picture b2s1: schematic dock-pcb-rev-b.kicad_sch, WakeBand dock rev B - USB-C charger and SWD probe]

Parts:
C1, C2: 15pF; C_0402_1005Metric; LCSC C1548
C3: 10uF; C_0603_1608Metric; LCSC C19702
C4, C5, C6, C7, C14, C15: 1uF; C_0402_1005Metric; LCSC C52923
C8, C9, C10, C11, C12, C13, C16, C17, C18, C19, C20, C21: 100nF; C_0402_1005Metric; LCSC C1525
D1: red USB; LED_0603_1608Metric; MPN KENTO KT-0603R; LCSC C2286
D2: red ACT; LED_0603_1608Metric; MPN KENTO KT-0603R; LCSC C2286
F1: 500mA; Fuse_0805_2012Metric; MPN FSMD050-0805-R; LCSC C181350
J1: USB-C; USB_C_Receptacle_HRO_TYPE-C-31-M-12; MPN HRO TYPE-C-31-M-12; LCSC C165948
P1: SWCLK; SpringPin_Mill-Max_0906_PTH_D1.4mm_Drill0.6mm; MPN Mill-Max 0906-4-15-20-75-14-11-0
P2: SWDIO; SpringPin_Mill-Max_0906_PTH_D1.4mm_Drill0.6mm; MPN Mill-Max 0906-4-15-20-75-14-11-0
P3: GND; SpringPin_Mill-Max_0906_PTH_D1.4mm_Drill0.6mm; MPN Mill-Max 0906-4-15-20-75-14-11-0
P4: VIN; SpringPin_Mill-Max_0906_PTH_D1.4mm_Drill0.6mm; MPN Mill-Max 0906-4-15-20-75-14-11-0
R1, R9, R13, R14: 1k; R_0402_1005Metric; LCSC C11702
R2, R3: 5.1k; R_0402_1005Metric; LCSC C25905
R4, R5: 27; R_0402_1005Metric; LCSC C25100
R6: 15k; R_0402_1005Metric; LCSC C25756
R7, R8: 10k; R_0402_1005Metric; LCSC C25744
R10, R11, R12: 22; R_0402_1005Metric; LCSC C25092
SW1: BOOTSEL; SW_SPST_TS-1088-xR020; MPN XKB TS-1088-AR02016; LCSC C720477
TP1: RP_SWCLK; TestPoint_Pad_D1.0mm
TP2: RP_SWDIO; TestPoint_Pad_D1.0mm
TP3: RUN; TestPoint_Pad_D1.0mm
TP4: GND; TestPoint_Pad_D1.0mm
U1: RP2040; QFN-56-1EP_7x7mm_P0.4mm_EP3.2x3.2mm; MPN Raspberry Pi RP2040; LCSC C2040
U2: W25Q16JVSNIQ; SOIC-8_3.9x4.9mm_P1.27mm; MPN Winbond W25Q16JVSNIQ; LCSC C2456211
U3: USBLC6-2SC6; SOT-23-6; MPN ST USBLC6-2SC6; LCSC C7519
U4: XC6206P332MR; SOT-23-3; MPN Torex XC6206P332MR; LCSC C2897477
U5: XC6206P182MR; SOT-23-3; MPN Torex XC6206P182MR; LCSC C21659
U6: SY6280AAC; SOT-23-5; MPN Silergy SY6280AAC; LCSC C55136
U7: 74LVC1T45; SOT-23-6; MPN Diodes 74LVC1T45W6-7; LCSC C168856
U8: TXS0101; SOT-23-6; MPN TI TXS0101DBVR; LCSC C132604
Y1: 12MHz 12pF; Crystal_SMD_3225-4Pin_3.2x2.5mm; MPN 3225-12-12-10-10/A; LCSC C2981639

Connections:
/+1V1: C15.1, C16.1, U1.23 (DVDD), U1.45 (VREG_VOUT), U1.50 (DVDD)
/+1V8: C5.1, C19.1, C21.1, U5.2 (VO), U7.6 (VCCB), U8.1 (V_{CCA}), U8.5 (OE)
/+3V3: C4.1, C8.1, C9.1, C10.1, C11.1, C12.1, C13.1, C14.1, C17.1, C18.1, C20.1, R7.1, R8.1, U1.1 (IOVDD), U1.10 (IOVDD), U1.22 (IOVDD), U1.33 (IOVDD), U1.42 (IOVDD), U1.43 (ADC_AVDD), U1.44 (VREG_VIN), U1.48 (USB_VDD), U1.49 (IOVDD), U2.8 (VCC), U4.2 (VO), U5.3 (VI), U7.1 (VCCA), U7.5 (DIR), U8.6 (V_{CCB})
/BOOT: R9.2, SW1.1
/CC1: J1.A5 (CC1), R2.1
/CC2: J1.B5 (CC2), R3.1
/GND: C1.2, C2.2, C3.2, C4.2, C5.2, C6.2, C7.2, C8.2, C9.2, C10.2, C11.2, C12.2, C13.2, C14.2, C15.2, C16.2, C17.2, C18.2, C19.2, C20.2, C21.2, J1.A1 (GND), J1.A12 (GND), J1.B1 (GND), J1.B12 (GND), J1.SH (SHIELD), P3.1, R2.2, R3.2, R6.2, R13.2, R14.2, SW1.2, TP4.1, U1.19 (TESTEN), U1.57 (GND), U2.4 (GND), U3.2 (GND), U4.1 (GND), U5.1 (GND), U6.2 (GND), U7.2 (GND), U8.2 (GND), Y1.2 (G), Y1.4 (G)
/ISET: R6.1, U6.3 (ISET)
/LED_ACT: D2.2 (A), U1.27 (GPIO16)
/LED_ACT_K: D2.1 (K), R14.1
/LED_USB: D1.2 (A), U1.4 (GPIO2)
/LED_USB_K: D1.1 (K), R13.1
/P_SWCLK: P1.1, R11.2
/P_SWDIO: P2.1, R12.2
/QSPI_SCLK: U1.52 (QSPI_SCLK), U2.6 (CLK)
/QSPI_SD0: U1.53 (QSPI_SD0), U2.5 (DI/IO_{0})
/QSPI_SD1: U1.55 (QSPI_SD1), U2.2 (DO/IO_{1})
/QSPI_SD2: U1.54 (QSPI_SD2), U2.3 (~WP/IO_{2})
/QSPI_SD3: U1.51 (QSPI_SD3), U2.7 (~HOLD/~RESET/IO_{3})
/QSPI_SS: R8.2, R9.1, U1.56 (~QSPI_SS), U2.1 (~CS)
/RP_SWCLK: TP1.1, U1.24 (SWCLK)
/RP_SWDIO: TP2.1, U1.25 (SWDIO)
/RUN: R7.2, TP3.1, U1.26 (RUN)
/SWCLK_1V8: R11.1, U7.4 (B)
/SWCLK_3V3: U1.15 (GPIO12), U7.3 (A)
/SWDIO_1V8: R12.1, U8.3 (A)
/SWDIO_3V3: R10.2, U1.16 (GPIO13), U8.4 (B)
/SWDIO_DRV: R10.1, U1.17 (GPIO14)
/USB_DM: J1.A7 (D-), J1.B7 (D-), R5.1, U3.3 (I/O2), U3.4 (I/O2)
/USB_DM_MCU: R5.2, U1.46 (USB_DM)
/USB_DP: J1.A6 (D+), J1.B6 (D+), R4.1, U3.1 (I/O1), U3.6 (I/O1)
/USB_DP_MCU: R4.2, U1.47 (USB_DP)
/VBUS: F1.1, J1.A4 (VBUS), J1.A9 (VBUS), J1.B4 (VBUS), J1.B9 (VBUS), U3.5 (VBUS)
/VBUS_F: C3.1, C6.1, F1.2, U4.3 (VI), U6.4 (EN), U6.5 (IN)
/VIN_BAND: C7.1, P4.1, U6.1 (OUT)
/XIN: C1.1, U1.20 (XIN), Y1.1
/XOUT: R1.1, U1.21 (XOUT)
/XOUT_X: C2.1, R1.2, Y1.3

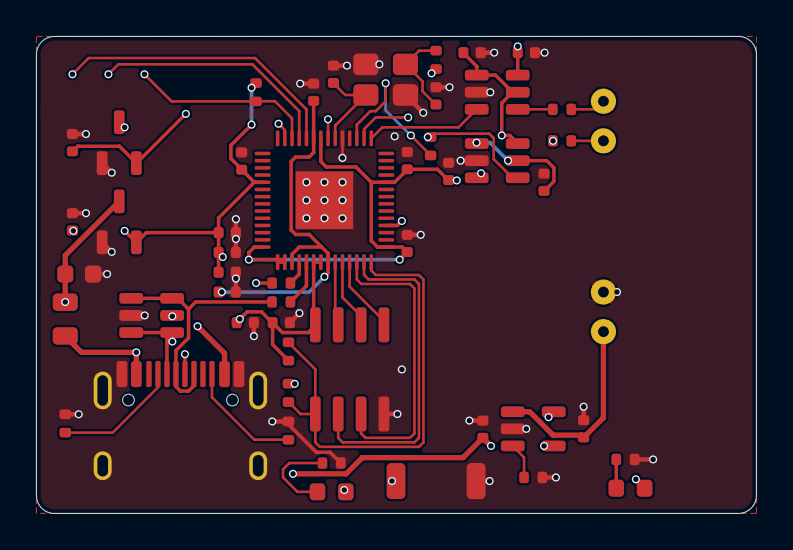
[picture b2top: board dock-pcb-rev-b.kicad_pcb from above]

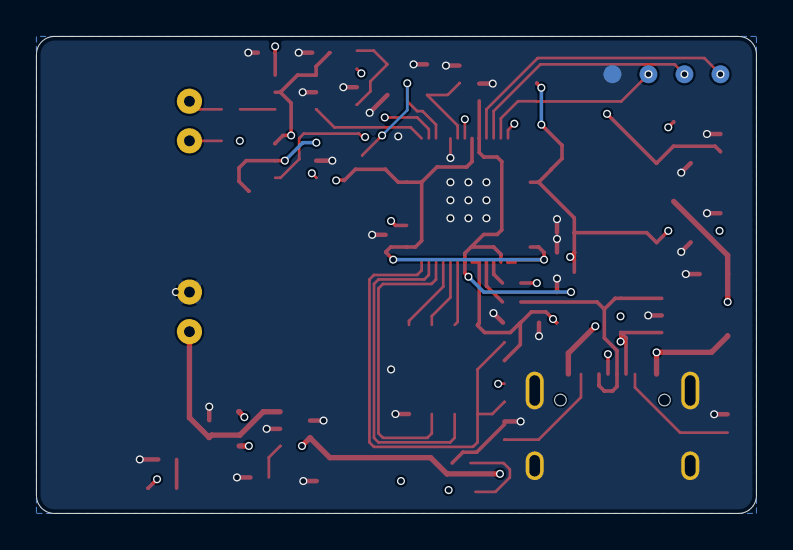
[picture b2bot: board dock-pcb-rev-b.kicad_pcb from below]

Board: 4 copper layers, 40.0 x 26.5 mm, 57 parts (4 on the bottom side), 38 nets.

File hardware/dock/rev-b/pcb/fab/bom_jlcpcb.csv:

Comment,Designator,Footprint,LCSC,MPN,Qty
RP2040,U1,QFN-56-1EP_7x7mm_P0.4mm_EP3.2x3.2mm,C2040,Raspberry Pi RP2040,1
W25Q16JVSNIQ,U2,SOIC-8_3.9x4.9mm_P1.27mm,C2456211,Winbond W25Q16JVSNIQ,1
12MHz 12pF,Y1,Crystal_SMD_3225-4Pin_3.2x2.5mm,C2981639,3225-12-12-10-10/A,1
15pF,"C1,C2",C_0402_1005Metric,C1548,,2
1k,"R1,R9,R13,R14",R_0402_1005Metric,C11702,,4
USB-C,J1,USB_C_Receptacle_HRO_TYPE-C-31-M-12,C165948,HRO TYPE-C-31-M-12,1
5.1k,"R2,R3",R_0402_1005Metric,C25905,,2
USBLC6-2SC6,U3,SOT-23-6,C7519,ST USBLC6-2SC6,1
27,"R4,R5",R_0402_1005Metric,C25100,,2
500mA,F1,Fuse_0805_2012Metric,C181350,FSMD050-0805-R,1
10uF,C3,C_0603_1608Metric,C19702,,1
XC6206P332MR,U4,SOT-23-3,C2897477,Torex XC6206P332MR,1
1uF,"C4,C5,C6,C7,C14,C15",C_0402_1005Metric,C52923,,6
XC6206P182MR,U5,SOT-23-3,C21659,Torex XC6206P182MR,1
SY6280AAC,U6,SOT-23-5,C55136,Silergy SY6280AAC,1
15k,R6,R_0402_1005Metric,C25756,,1
100nF,"C8,C9,C10,C11,C12,C13,C16,C17,C18,C19,C20,C21",C_0402_1005Metric,C1525,,12
10k,"R7,R8",R_0402_1005Metric,C25744,,2
BOOTSEL,SW1,SW_SPST_TS-1088-xR020,C720477,XKB TS-1088-AR02016,1
74LVC1T45,U7,SOT-23-6,C168856,Diodes 74LVC1T45W6-7,1
TXS0101,U8,SOT-23-6,C132604,TI TXS0101DBVR,1
22,"R10,R11,R12",R_0402_1005Metric,C25092,,3
red LED,"D1,D2",LED_0603_1608Metric,C2286,KENTO KT-0603R,2
